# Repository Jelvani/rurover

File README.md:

# Rutgers Rover (RURover) User Guide (Under Develpoment)

RURover is an unmaned-ground-vehicke (UGV) based on the [Traxxas X-Maxx 8s](https://traxxas.com/products/landing/x-maxx/), that has been modified with the addition of wheel encoders, steering sensor, and an on-board embedded system.

## Hardware
***
A list of all additional hardware added to RURover can be found below:
- Sensors
    - [Wheel encoders (X4)](https://www.usdigital.com/products/encoders/incremental/shaft/S4T)
    - [Steering angle encoder](https://www.usdigital.com/products/encoders/absolute/magnetic/MA3)
    - [Inertial Measurement Unit (IMU)](https://www.adafruit.com/product/2472)
- Embedded System
    - [System on module, NVIDIA Jetson TX2](https://developer.nvidia.com/embedded/jetson-tx2-developer-kit)
    - [Jetson TX2 custom carrier board](https://www.uta.edu/utari/research/robotics/airborne/tutorials.php#TX2version2)
    - [Teensy 4.0 microcontroller](https://www.pjrc.com/store/teensy40.html)
- Batteries
    - [6500 mAh 4s LiPo (X2)](https://www.amazon.com/Youme-Battery-6500mAh-Traxxas-%EF%BC%8CHelicopter%EF%BC%8CAirplane/dp/B07PD2CNQM/ref=sr_1_7?dchild=1&keywords=4s+lipo+traxxas+connector&qid=1598924690&sr=8-7)

## Robot Operating System (ROS) Specifications
***

## Connecting to the platform
***
1. Choose the wifi network with SSID `rurover` and password is `rurover-ram-lab`.
2. SSH into the TX2 with `ssh rurover@10.42.0.1` and password is `12`.

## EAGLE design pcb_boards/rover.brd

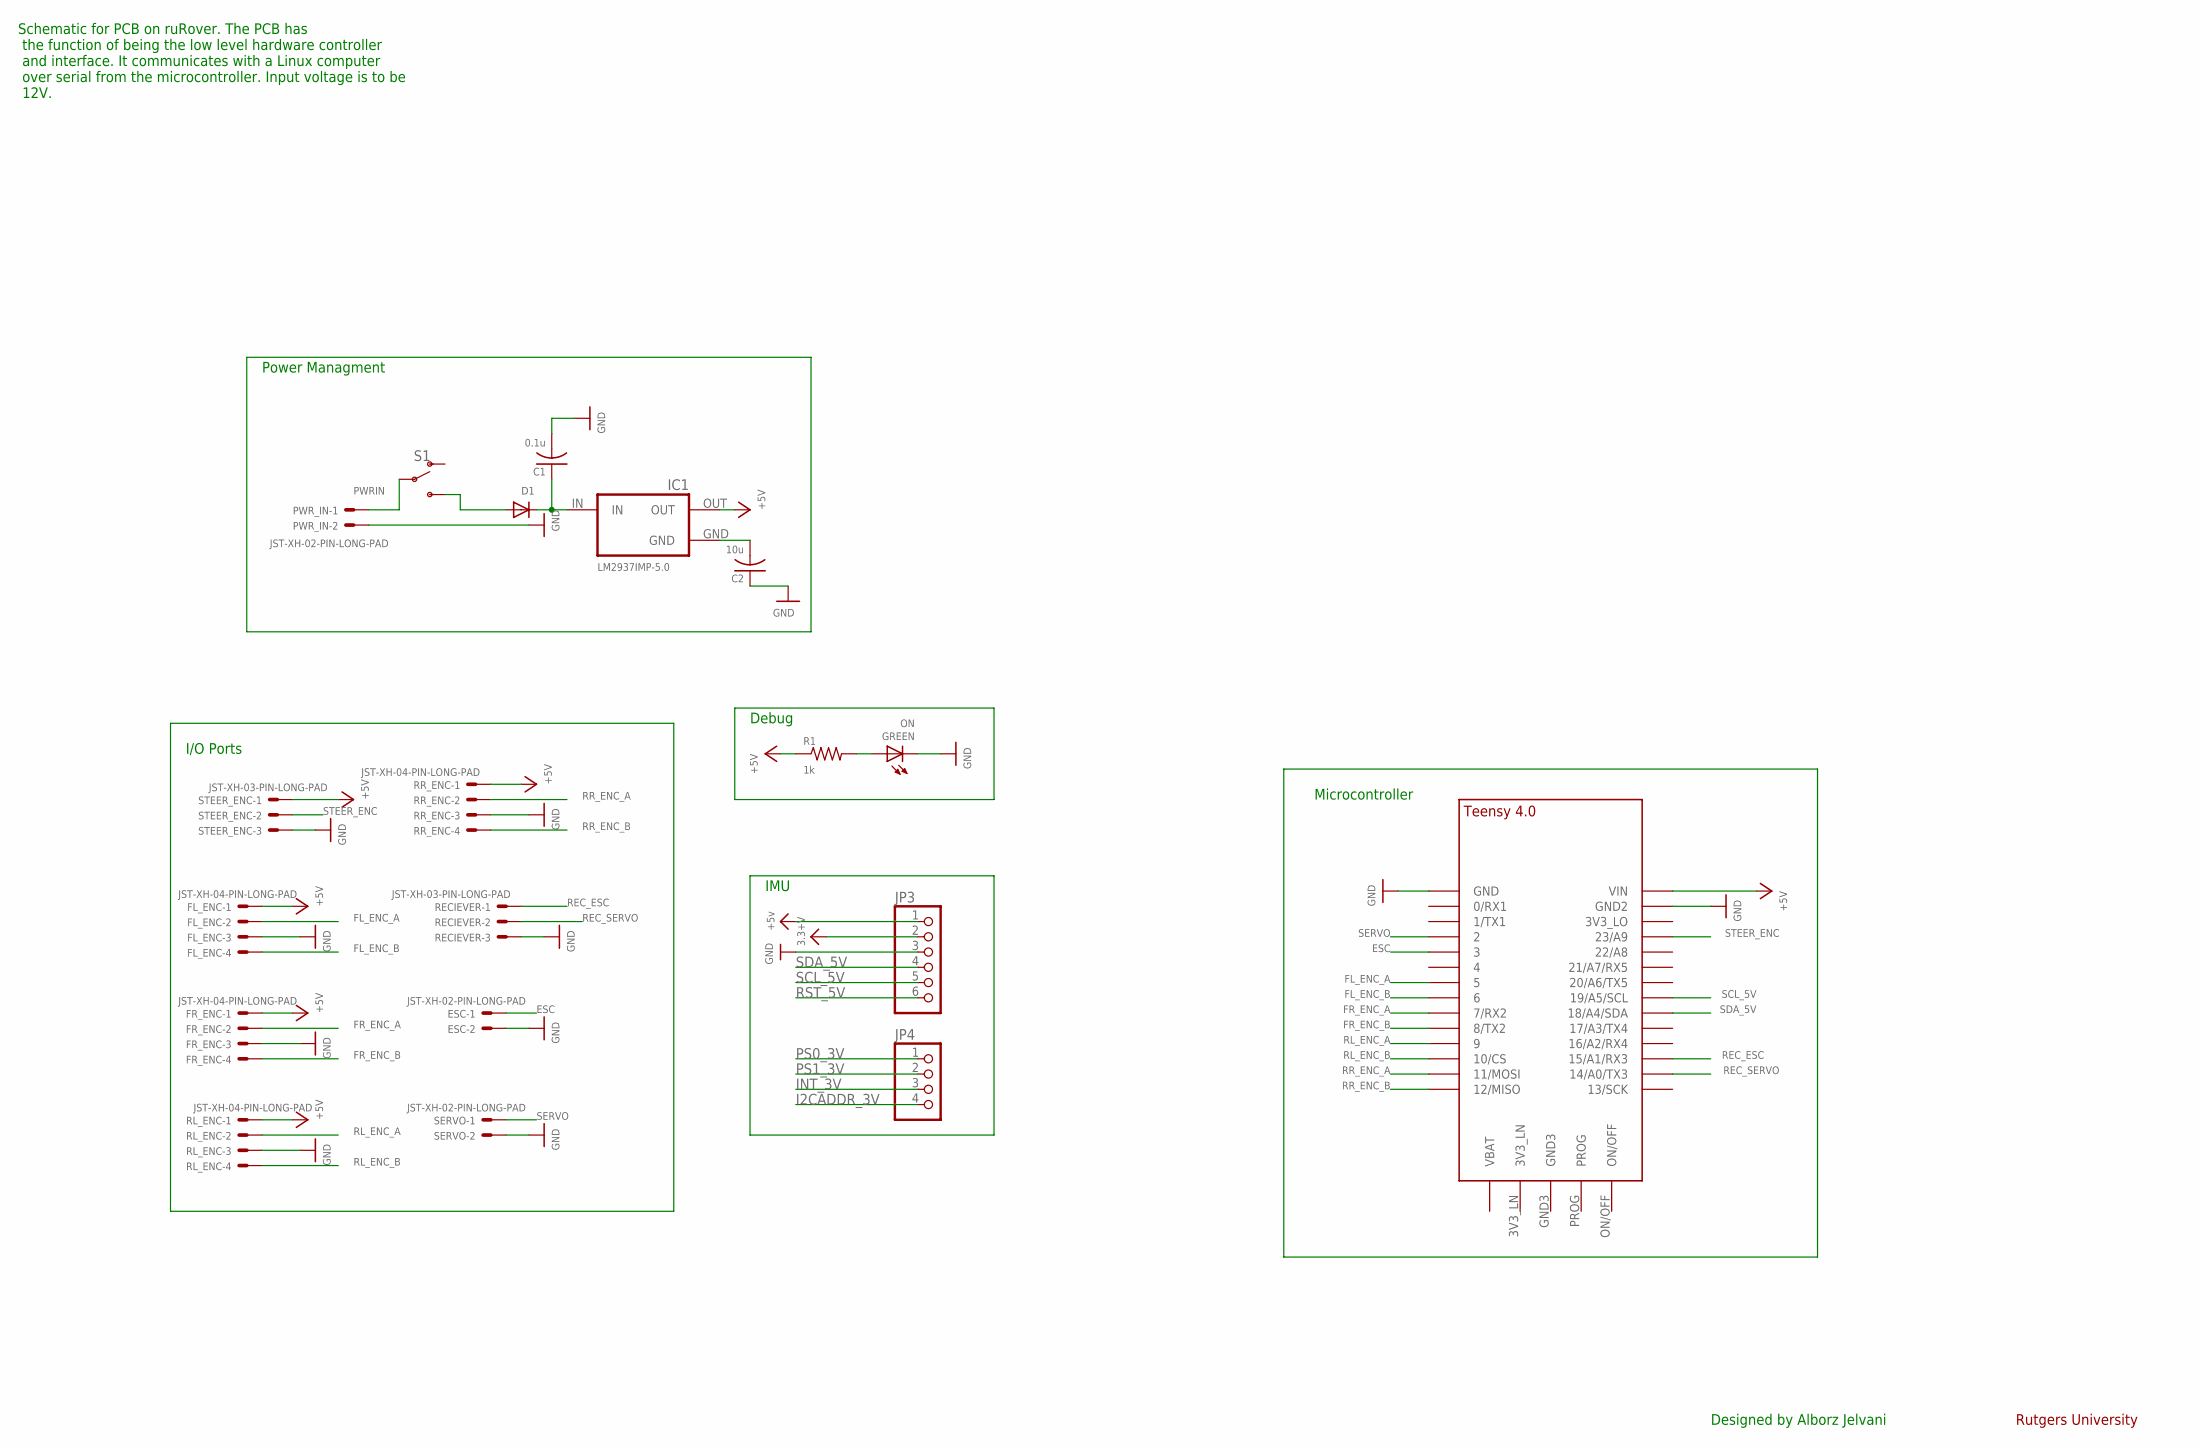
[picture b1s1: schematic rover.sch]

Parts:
C1: 0.1u; C1206
C2: 10u; C1206
D1: DIODESMA; SMADIODE
ESC: JST-XH-02-PIN-LONG-PAD; JST-XH-02-PACKAGE-LONG-PAD
FL_ENC: JST-XH-04-PIN-LONG-PAD; JST-XH-04-PACKAGE-LONG-PAD
FR_ENC: JST-XH-04-PIN-LONG-PAD; JST-XH-04-PACKAGE-LONG-PAD
GREEN: ON; CHIP-LED0805
IC1: LM2937IMP-5.0; SOT223
JP3: HEADER-1X676MIL; 1X06_ROUND_76
JP4: HEADER-1X476MIL; 1X04_ROUND_76
PWR_IN: JST-XH-02-PIN-LONG-PAD; JST-XH-02-PACKAGE-LONG-PAD
R1: 1k; R0603
RECIEVER: JST-XH-03-PIN-LONG-PAD; JST-XH-03-PACKAGE-LONG-PAD
RL_ENC: JST-XH-04-PIN-LONG-PAD; JST-XH-04-PACKAGE-LONG-PAD
RR_ENC: JST-XH-04-PIN-LONG-PAD; JST-XH-04-PACKAGE-LONG-PAD
S1: SWITCH-SPDT-SMD-AYZ0202; SWITCH_DPDT_SMD_AYZ0202
SERVO: JST-XH-02-PIN-LONG-PAD; JST-XH-02-PACKAGE-LONG-PAD
STEER_ENC: JST-XH-03-PIN-LONG-PAD; JST-XH-03-PACKAGE-LONG-PAD
U$5: TEENSY_4.0-BASIC

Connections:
+3.3V: JP3.2
+5V: FL_ENC.1, FR_ENC.1, IC1.OUT, JP3.1, R1.1, RL_ENC.1, RR_ENC.1, STEER_ENC.1, U$5.VIN
ESC: ESC.1, U$5.3/CANTX (3)
FL_ENC_A: FL_ENC.2, U$5.5
FL_ENC_B: FL_ENC.4, U$5.6
FR_ENC_A: FR_ENC.2, U$5.7 (7/RX2)
FR_ENC_B: FR_ENC.4, U$5.8 (8/TX2)
GND: C1.2, C2.1, ESC.2, FL_ENC.3, FR_ENC.3, GREEN.C, IC1.GND@ (GND), JP3.3, PWR_IN.2, RECIEVER.3, RL_ENC.3, RR_ENC.3, SERVO.2, STEER_ENC.3, U$5.GND, U$5.GND2
I2CADDR_3V: JP4.4
INT_3V: JP4.3
unnamed: GREEN.A, R1.2
unnamed: C1.1, D1.C, IC1.IN
unnamed: D1.A, S1.3 (S)
unnamed: C2.2, IC1.GND
PS0_3V: JP4.1
PS1_3V: JP4.2
PWRIN: PWR_IN.1, S1.2
REC_ESC: RECIEVER.1, U$5.15/A1 (15/A1/RX3)
REC_SERVO: RECIEVER.2, U$5.14/A0 (14/A0/TX3)
RL_ENC_A: RL_ENC.2, U$5.9/CS (9)
RL_ENC_B: RL_ENC.4, U$5.10/CS
RR_ENC_A: RR_ENC.2, U$5.11/MOSI
RR_ENC_B: RR_ENC.4, U$5.12/MISO
RST_5V: JP3.6
SCL_5V: JP3.5, U$5.19/A5/SCL
SDA_5V: JP3.4, U$5.18/A4/SDA
SERVO: SERVO.1, U$5.2
STEER_ENC: STEER_ENC.2, U$5.23/A9

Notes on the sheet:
Rutgers University
Power Managment
I/O Ports
Debug
IMU
Microcontroller
Schematic for PCB on ruRover. The PCB has the function of being the low level hardware controller and interface. It communicates with a Linux computer over serial from the microcontroller. Input voltage is to be 12V.
Designed by Alborz Jelvani

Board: 2 copper layers, 23 parts (0 on the bottom side), 22 nets, no tracks yet.

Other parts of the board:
U$4, U$6, U$7, U$8: 3,6

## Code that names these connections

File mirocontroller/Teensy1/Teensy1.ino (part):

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#define USE_TEENSY_HW_SERIAL

/****PIN CONNECTION MACROS****/
#define _SERVO 2
#define _ESC 3
#define _FL_A 5
#define _FL_B 6
#define _FR_A 7
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#define _RL_B 10
#define _RR_A 11
#define _RR_B 12
#define _REC_SERVO 14
#define _REC_ESC 15
#define _STEER 23
/*******Reciever PWM range macros*********/
#define _REC_ESC_MIN 1065
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
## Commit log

2020-07-24 initial
2020-07-25 added led and power switch
2020-07-25 added design blocks for imu and microcontroller
2020-07-27 added esc and servo headers
2020-07-27 added ground planes
2020-07-29 organized schematic
2020-08-10 finished pcb, added BOM
2020-08-15 began microcontroller code
2020-08-17 updated truck microcontroller code
2020-08-19 alpha stage for manual control testing and data collection with ROS
2020-08-19 added ackerman rosserial message headers folder
2020-08-19 working on fixing esc and servo noise problem
2020-08-21 updated code, fixed interrupt issues
2020-09-06 added drive mode selection, fixed steering calab bug
2020-09-07 added readme
2020-09-20 changed LDO regulator to active one in stock
2020-09-21 updated disconnet from rosserial issue
2020-09-28 added oscilloscope screenshots

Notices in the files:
parts and their libraries:
SparkFun-Switches: Licensing: Creative Commons ShareAlike 4.0 International - https://creativecommons.org/licenses/by-sa/4.0
microbuilder: This work is placed in the public domain, and may be freely used for commercial and non-commercial work with the following conditions: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
